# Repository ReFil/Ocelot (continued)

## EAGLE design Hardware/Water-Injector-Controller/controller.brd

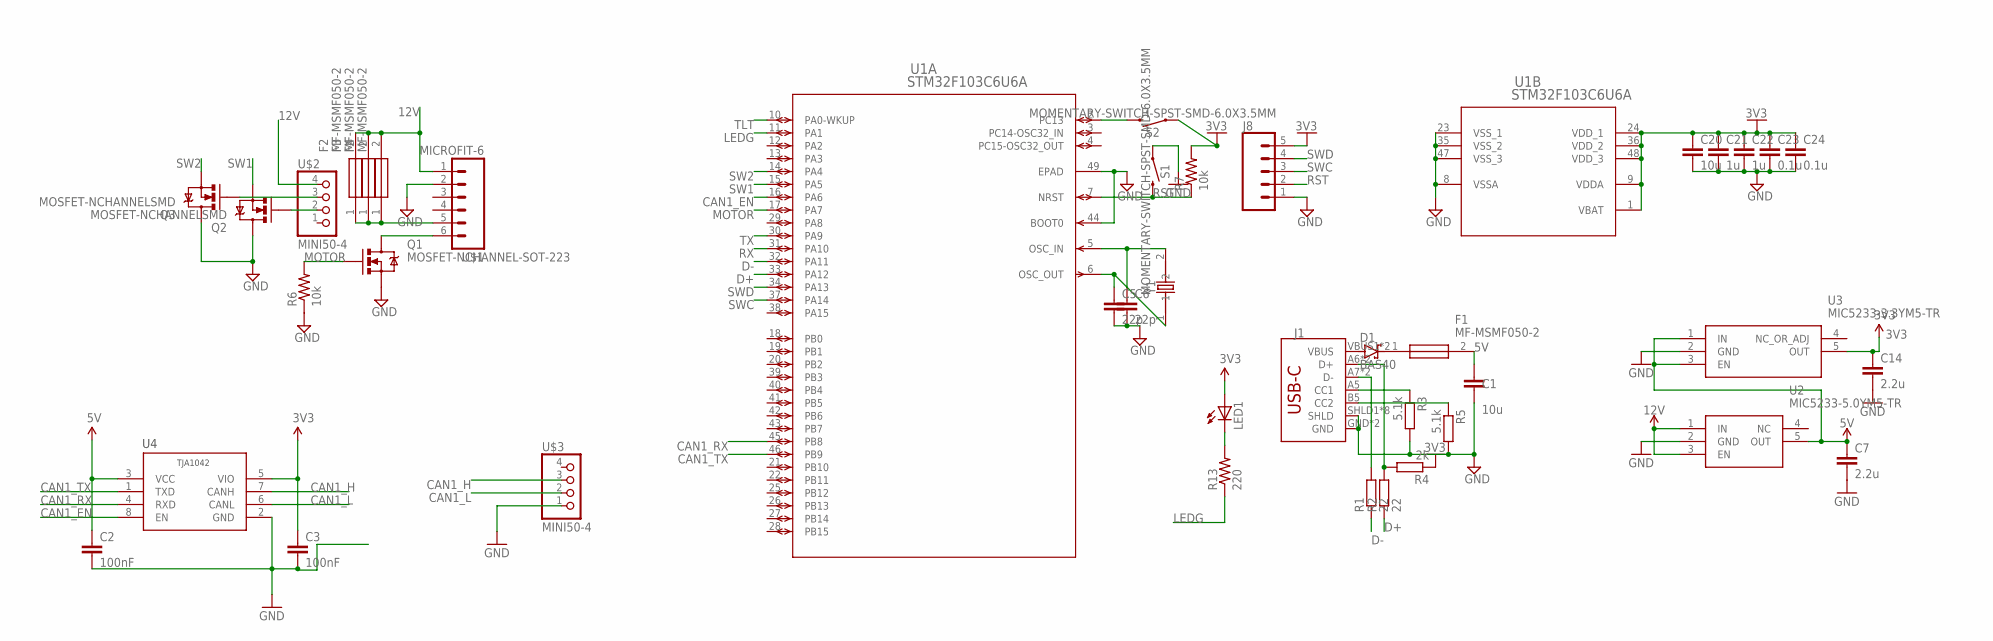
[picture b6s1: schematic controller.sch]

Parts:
C1: 10u; 0603-C
C2, C3: 100nF; 0603-C
C5, C6: 22p; C1206
C7, C14: 2.2u; C0603
C20: 10u; C1206
C21, C22: 1u; C1206
C23, C24: 0.1u; C1206
D1: BAS40; SOT23
F1, F2, F3, F4: MF-MSMF050-2; FUSC4632X85N
J1: SPARKFUN-CONNECTORS_USB_C16PIN; SPARKFUN-CONNECTORS_USB-C-16P
J8: CONN_051.27MM; 1X05_1.27MM
LED1: LEDCHIPLED_0805; CHIPLED_0805
Q1: MOSFET-NCHANNEL-SOT-223; SOT-223
Q2, Q3: MOSFET-NCHANNELSMD; SOT23-3
R1, R2: 22; R1206
R3, R5: 5.1k; R1206
R4: 2k; R1206
R6, R7: 10k; 0402-R
R13: 220; 0402-R
S1, S2: MOMENTARY-SWITCH-SPST-SMD-6.0X3.5MM; TACTILE_SWITCH_SMD_6.0X3.5MM
U1: STM32F103C6U6A; UFQFPN-48_7X7X0P55MM
U2: MIC5233-5.0YM5-TR; SOT95P280X145-5N
U3: MIC5233-3.3YM5-TR; SOT95P280X145-5N
U4: TJA1042; NXP_SEMICONDUCTORS_TJA1042T-3-CM_118_0
U$1: MICROFIT-6
U$2, U$3: MINI50-4; MINI50
Y1: 8MHz; OSCCC500X320X135

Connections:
3V3: C3.1, C14.1, C20.1, C21.1, C22.1, C23.1, C24.1, J8.5, LED1.A, R4.1, R7.2, S2.1, U1.1 (VBAT), U1.9 (VDDA), U1.24 (VDD_1), U1.36 (VDD_2), U1.48 (VDD_3), U3.5 (OUT), U4.5 (VIO)
5V: C1.1, C2.1, C7.1, F1.2, U2.5 (OUT), U3.1 (IN), U3.3 (EN), U4.3 (VCC)
12V: F2.2, F3.2, F4.2, U2.1 (IN), U2.3 (EN), U$1.1, U$2.4 (1)
CAN1_EN: U1.16 (PA6), U4.8 (EN)
CAN1_H: U4.7 (CANH), U$3.3 (2)
CAN1_L: U4.6 (CANL), U$3.2 (3)
CAN1_RX: U1.45 (PB8), U4.4 (RXD)
CAN1_TX: U1.46 (PB9), U4.1 (TXD)
D+: R2.1, U1.33 (PA12)
D-: R1.1, U1.32 (PA11)
GND: C1.2, C2.2, C3.2, C5.2, C6.2, C7.2, C14.2, C20.2, C21.2, C22.2, C23.2, C24.2, J1.GND, J1.GND2 (GND), J1.SHLD1 (SHLD), J1.SHLD2 (SHLD), J1.SHLD3 (SHLD), J1.SHLD4 (SHLD), J1.SHLD5 (SHLD), J1.SHLD6 (SHLD), J1.SHLD7 (SHLD), J1.SHLD8 (SHLD), J8.1, Q1.3 (S), Q2.3 (D), Q3.3 (D), R3.2, R5.2, R6.1, S1.1, U1.8 (VSSA), U1.23 (VSS_1), U1.35 (VSS_2), U1.44 (BOOT0), U1.47 (VSS_3), U1.49 (EPAD), U2.2 (GND), U3.2 (GND), U4.2 (GND), U$1.2, U$3.1 (4)
LEDG: R13.1, U1.11 (PA1)
MOTOR: Q1.1 (G), R6.2, U1.17 (PA7)
unnamed: S2.2, U1.2 (PC13)
unnamed: Q2.1 (G), U$2.2 (3)
unnamed: F2.1, F3.1, F4.1, U$1.5
unnamed: Q3.1 (G), U$2.3 (2)
unnamed: Q1.2 (D), Q1.4 (D), U$1.6
unnamed: D1.1 (A), J1.VBUS1 (VBUS), J1.VBUS2 (VBUS)
unnamed: D1.3 (C), F1.1
unnamed: C6.1, U1.5 (OSC_IN), Y1.2
unnamed: C5.1, U1.6 (OSC_OUT), Y1.1
unnamed: J1.A5 (CC1), R3.1
unnamed: J1.B5 (CC2), R5.1
unnamed: J1.A7 (D-), J1.B7 (D-), R1.2
unnamed: J1.A6 (D+), J1.B6 (D+), R2.2, R4.2
unnamed: LED1.C, R13.2
RST: J8.2, R7.1, S1.2, U1.7 (NRST)
RX: U1.31 (PA10)
SW1: Q2.2 (S), U1.15 (PA5)
SW2: Q3.2 (S), U1.14 (PA4)
SWC: J8.3, U1.37 (PA14)
SWD: J8.4, U1.34 (PA13)
TLT: U1.10 (PA0-WKUP)
TX: U1.30 (PA9)

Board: 2 copper layers, 41 parts (0 on the bottom side), 32 nets, no tracks yet.

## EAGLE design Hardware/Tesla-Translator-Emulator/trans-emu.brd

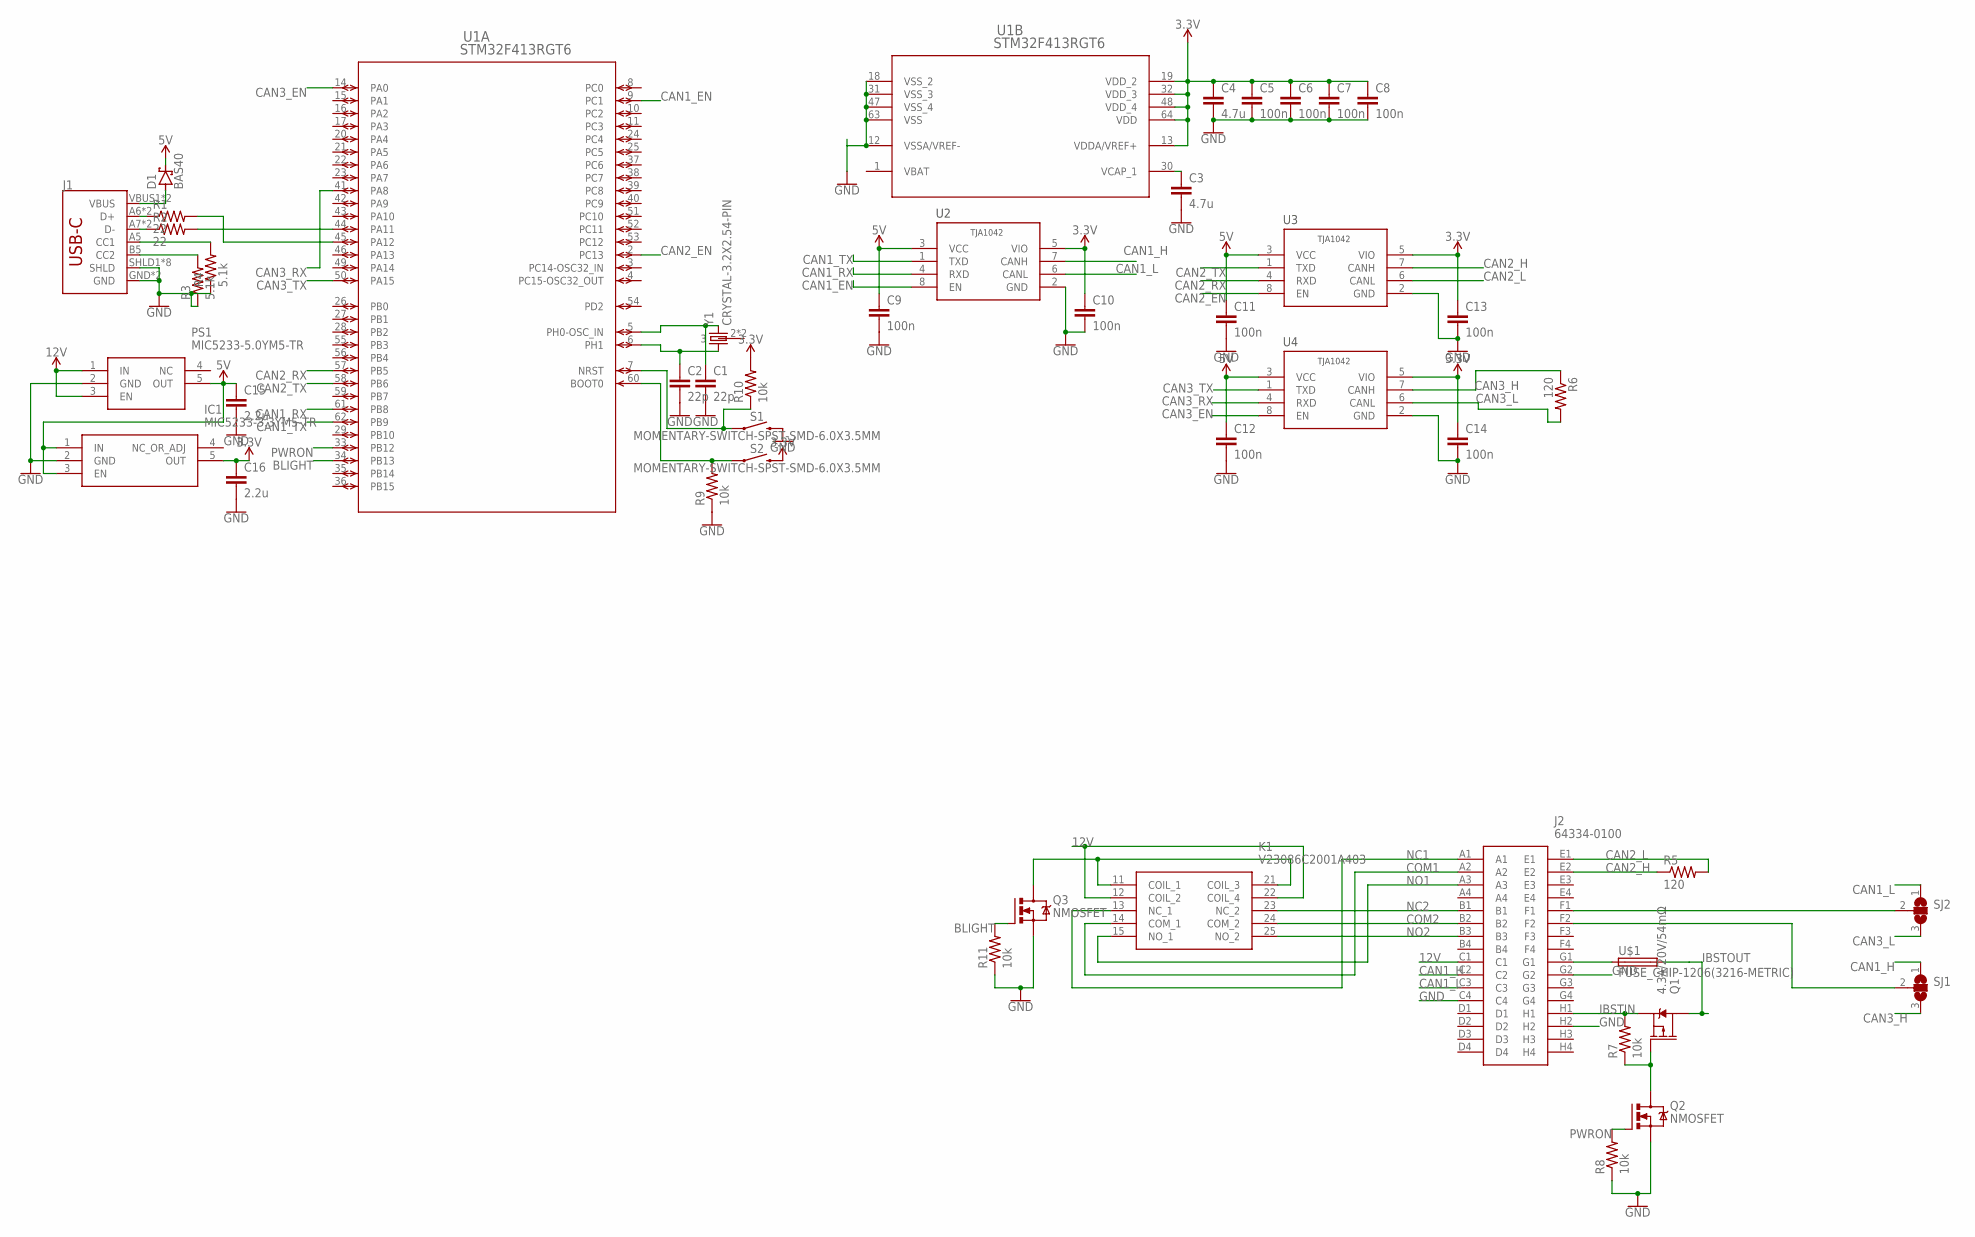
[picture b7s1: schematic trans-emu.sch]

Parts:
C1, C2: 22p; 0603-C
C3, C4: 4.7u; 0603-C
C5, C6, C7, C8, C9, C10, C11, C12, C13, C14: 100n; 0603-C
C15, C16: 2.2u; 0603-C
D1: BAS40; SOT23
IC1: MIC5233-3.3YM5-TR; SOT95P280X145-5N
J1: USB-C-BREAKOUT_SPARKFUN-CONNECTORS_USB_C16PIN; USB-C-BREAKOUT_SPARKFUN-CONNECTORS_USB-C-16P
J2: 64334-0100; 643340100
K1: V23086C2001A403
PS1: MIC5233-5.0YM5-TR; SOT95P280X145-5N
Q1: 4.3A/20V/54mΩ; SOT23-3
Q2, Q3: NMOSFET; SOT23
R1, R2: 22; 0402-R
R3, R4: 5.1k; 0402-R
R5, R6: 120; 0402-R
R7, R8, R9, R10, R11: 10k; 0402-R
S1, S2: MOMENTARY-SWITCH-SPST-SMD-6.0X3.5MM; TACTILE_SWITCH_SMD_6.0X3.5MM
SJ1, SJ2: SJ2W; SJ_2
U1: STM32F413RGT6; LQFP64-10X10MM
U2, U3, U4: TJA1042; NXP_SEMICONDUCTORS_TJA1042T-3-CM_118_0
U$1: FUSE_CHIP-1206(3216-METRIC); FUSC3215X82N
Y1: CRYSTAL-3.2X2.54-PIN; XTAL-3.2X2.5

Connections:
3.3V: C4.1, C5.1, C6.1, C7.1, C8.1, C10.1, C13.1, C14.1, C16.1, IC1.5 (OUT), R10.2, S2.2, U1.13 (VDDA/VREF+), U1.19 (VDD_2), U1.32 (VDD_3), U1.48 (VDD_4), U1.64 (VDD), U2.5 (VIO), U3.5 (VIO), U4.5 (VIO)
5V: C9.1, C11.1, C12.1, C15.1, D1.3 (C), IC1.1 (IN), IC1.3 (EN), PS1.5 (OUT), U2.3 (VCC), U3.3 (VCC), U4.3 (VCC)
12V: J2.C1, K1.12 (COIL_2), K1.22 (COIL_4), PS1.1 (IN), PS1.3 (EN)
BLIGHT: Q3.1 (G), R11.2, U1.34 (PB13)
CAN1_EN: U1.9 (PC1), U2.8 (EN)
CAN1_H: J2.C2, SJ1.1, U2.7 (CANH)
CAN1_L: J2.C3, SJ2.1, U2.6 (CANL)
CAN1_RX: U1.61 (PB8), U2.4 (RXD)
CAN1_TX: U1.62 (PB9), U2.1 (TXD)
CAN2_EN: U1.2 (PC13), U3.8 (EN)
CAN2_H: J2.E2, R5.1, U3.7 (CANH)
CAN2_L: J2.E1, R5.2, U3.6 (CANL)
CAN2_RX: U1.57 (PB5), U3.4 (RXD)
CAN2_TX: U1.58 (PB6), U3.1 (TXD)
CAN3_EN: U1.14 (PA0), U4.8 (EN)
CAN3_H: R6.1, SJ1.3, U4.7 (CANH)
CAN3_L: R6.2, SJ2.3, U4.6 (CANL)
CAN3_RX: U1.41 (PA8), U4.4 (RXD)
CAN3_TX: U1.50 (PA15), U4.1 (TXD)
COM1: J2.A2, K1.14 (COM_1)
COM2: J2.B2, K1.24 (COM_2)
GND: C1.2, C2.2, C3.2, C4.2, C5.2, C6.2, C7.2, C8.2, C9.2, C10.2, C11.2, C12.2, C13.2, C14.2, C15.2, C16.2, IC1.2 (GND), J1.GND, J1.GND2 (GND), J1.SHLD1 (SHLD), J1.SHLD2 (SHLD), J1.SHLD3 (SHLD), J1.SHLD4 (SHLD), J1.SHLD5 (SHLD), J1.SHLD6 (SHLD), J1.SHLD7 (SHLD), J1.SHLD8 (SHLD), J2.C4, J2.G2, J2.H2, PS1.2 (GND), Q2.2 (S), Q3.2 (S), R3.1, R4.1, R8.1, R9.1, R11.1, S1.2, U1.12 (VSSA/VREF-), U1.18 (VSS_2), U1.31 (VSS_3), U1.47 (VSS_4), U1.63 (VSS), U2.2 (GND), U3.2 (GND), U4.2 (GND)
IBSTIN: J2.H1, Q1.2 (S), R7.2
IBSTOUT: Q1.3 (D), U$1.2
unnamed: C1.1, U1.5 (PH0-OSC_IN), Y1.3 (2)
unnamed: C2.1, U1.6 (PH1), Y1.1
unnamed: R2.2, U1.44 (PA11)
unnamed: R1.2, U1.45 (PA12)
unnamed: D1.1 (A), J1.VBUS1 (VBUS), J1.VBUS2 (VBUS)
unnamed: J1.A5 (CC1), R4.2
unnamed: J1.B5 (CC2), R3.2
unnamed: R10.1, S1.1, U1.7 (NRST)
unnamed: R9.2, S2.1, U1.60 (BOOT0)
unnamed: J1.A6 (D+), J1.B6 (D+), R1.1
unnamed: J1.A7 (D-), J1.B7 (D-), R2.1
unnamed: J2.F2, SJ1.2
unnamed: C3.1, U1.30 (VCAP_1)
unnamed: J2.F1, SJ2.2
unnamed: Q1.1 (G), Q2.3 (D), R7.1
unnamed: K1.11 (COIL_1), K1.21 (COIL_3), Q3.3 (D)
unnamed: J2.G1, U$1.1
NC1: J2.A1, K1.13 (NC_1)
NC2: J2.B1, K1.23 (NC_2)
NO1: J2.A3, K1.15 (NO_1)
NO2: J2.B3, K1.25 (NO_2)
PWRON: Q2.1 (G), R8.2, U1.33 (PB12)
VBAT: U1.1 (VBAT)

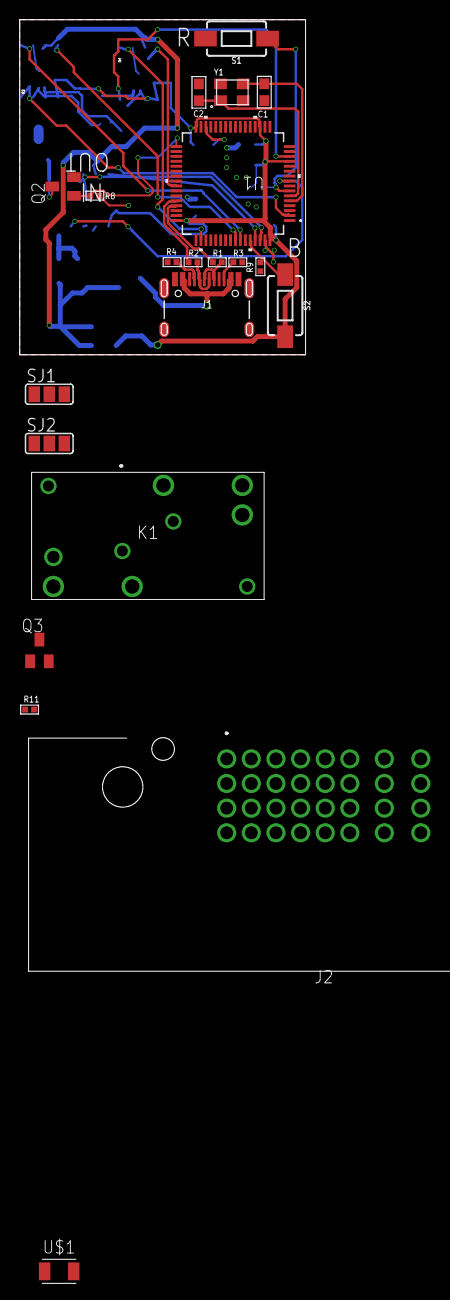
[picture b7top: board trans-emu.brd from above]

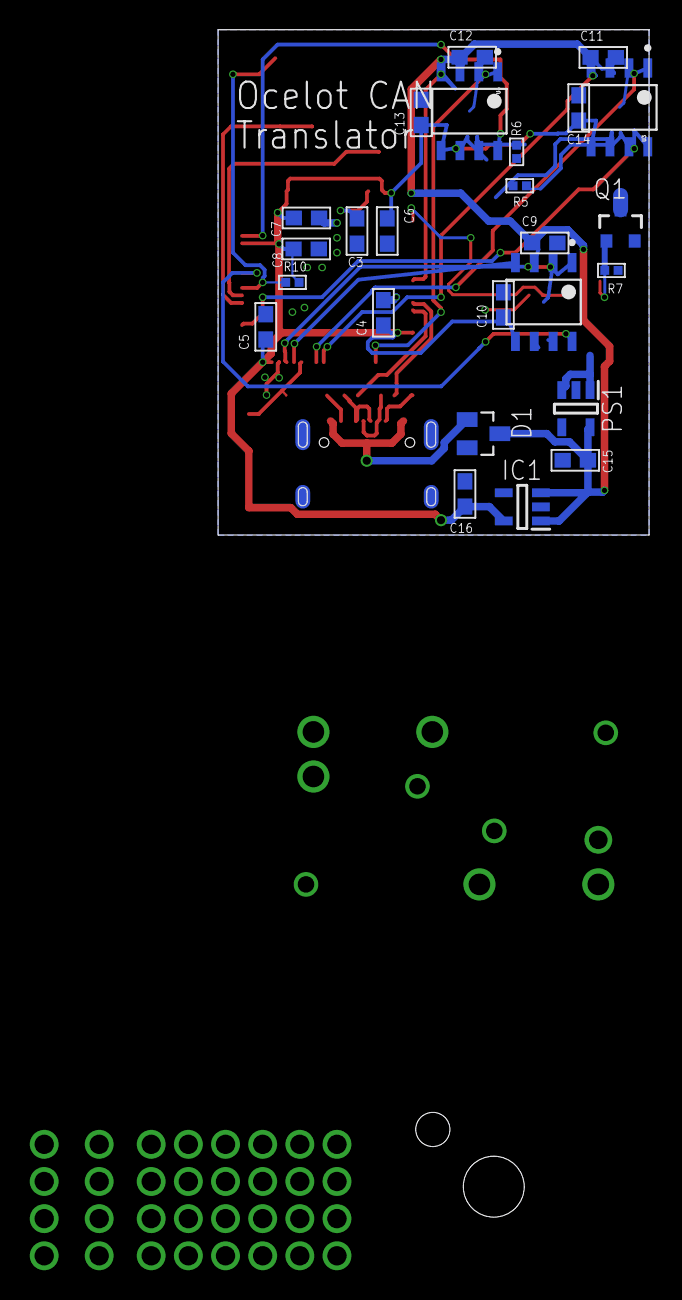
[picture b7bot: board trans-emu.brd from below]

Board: 2 copper layers, 29.0 x 34.0 mm, 46 parts (25 on the bottom side), 46 nets.

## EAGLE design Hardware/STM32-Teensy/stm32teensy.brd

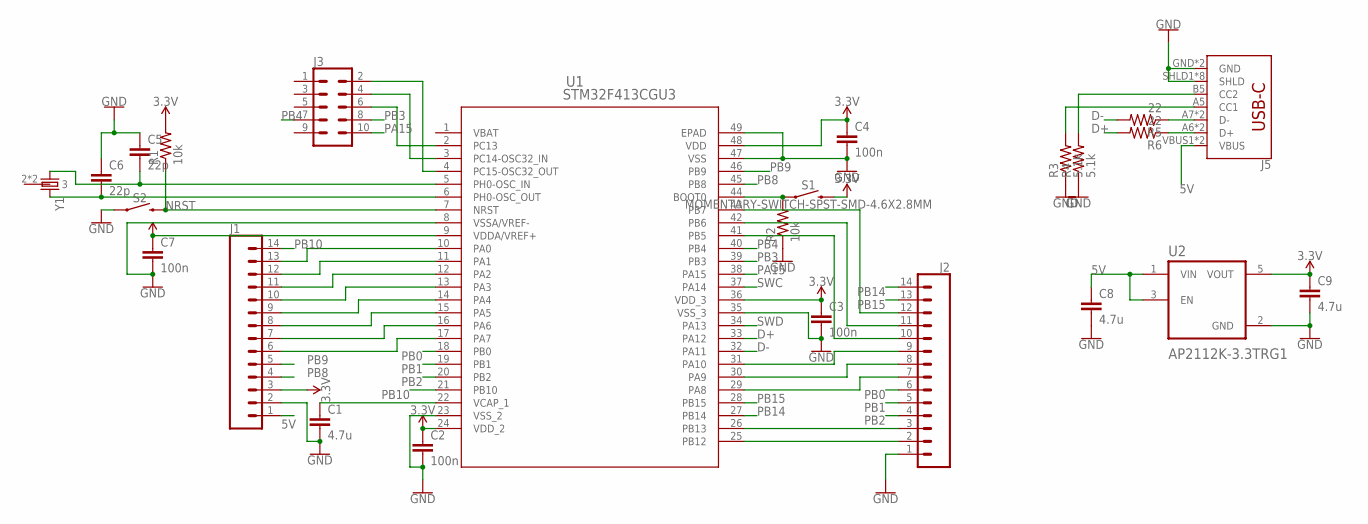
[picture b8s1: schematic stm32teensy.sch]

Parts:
C1, C8, C9: 4.7u; 0402-C
C2, C3, C4, C7: 100n; 0402-C
C5, C6: 22p; 0402-C
J1, J2: CONN_14; 1X14
J3: CONN_05X2SHD_SMD; 2X5-SHROUDED_SMD
J5: SPARKFUN-CONNECTORS_USB_C16PIN; SPARKFUN-CONNECTORS_USB-C-16P
R1, R2: 10k; 0402-R
R3, R4: 5.1k; 0402-R
R5, R6: 22; 0402-R
S1, S2: MOMENTARY-SWITCH-SPST-SMD-4.6X2.8MM; TACTILE_SWITCH_SMD_4.6X2.8MM
U1: STM32F413CGU3; UFQFPN_13CGU3_STM
U2: AP2112K-3.3TRG1; SOT95P285X140-5N
Y1: CRYSTAL-3.2X2.54-PIN; XTAL-3.2X2.5

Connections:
3.3V: C2.1, C3.1, C4.1, C7.1, C9.1, J1.3, R1.2, S1.3 (2), S1.4 (2), U1.9 (VDDA/VREF+), U1.24 (VDD_2), U1.36 (VDD_3), U1.48 (VDD), U2.5 (VOUT)
5V: C8.1, J1.1, J5.VBUS1 (VBUS), J5.VBUS2 (VBUS), U2.1 (VIN), U2.3 (EN)
D+: R6.2, U1.33 (PA12)
D-: R5.2, U1.32 (PA11)
GND: C1.2, C2.2, C3.2, C4.2, C5.1, C6.1, C7.2, C8.2, C9.2, J1.2, J2.1, J5.GND, J5.GND2 (GND), J5.SHLD1 (SHLD), J5.SHLD2 (SHLD), J5.SHLD3 (SHLD), J5.SHLD4 (SHLD), J5.SHLD5 (SHLD), J5.SHLD6 (SHLD), J5.SHLD7 (SHLD), J5.SHLD8 (SHLD), R2.1, R3.1, R4.1, S2.1, S2.2 (1), U1.8 (VSSA/VREF-), U1.23 (VSS_2), U1.35 (VSS_3), U1.47 (VSS), U1.49 (EPAD), U2.2 (GND)
unnamed: J3.6, U1.2 (PC13)
unnamed: R2.2, S1.1, S1.2 (1), U1.44 (BOOT0)
unnamed: C6.2, U1.6 (PH0-OSC_OUT), Y1.3 (2)
unnamed: C5.2, U1.5 (PH0-OSC_IN), Y1.1
unnamed: J1.13, U1.10 (PA0)
unnamed: J2.10, U1.41 (PB5)
unnamed: C1.1, U1.22 (VCAP_1)
unnamed: J1.12, U1.11 (PA1)
unnamed: J1.11, U1.12 (PA2)
unnamed: J1.10, U1.13 (PA3)
unnamed: J1.9, U1.14 (PA4)
unnamed: J1.8, U1.15 (PA5)
unnamed: J1.7, U1.16 (PA6)
unnamed: J1.6, U1.17 (PA7)
unnamed: J2.2, U1.25 (PB12)
unnamed: J2.3, U1.26 (PB13)
unnamed: J2.11, U1.42 (PB6)
unnamed: J2.12, U1.43 (PB7)
unnamed: J2.7, U1.29 (PA8)
unnamed: J2.8, U1.30 (PA9)
unnamed: J2.9, U1.31 (PA10)
unnamed: J3.4, U1.3 (PC14-OSC32_IN)
unnamed: J3.2, U1.4 (PC15-OSC32_OUT)
unnamed: J5.A7 (D-), J5.B7 (D-), R5.1
unnamed: J5.A6 (D+), J5.B6 (D+), R6.1
unnamed: J5.A5 (CC1), R3.2
unnamed: J5.B5 (CC2), R4.2
NRST: R1.1, S2.3 (2), S2.4 (2), U1.7 (NRST)
PA15: J3.10, U1.38 (PA15)
PB0: J2.6, U1.18 (PB0)
PB1: J2.5, U1.19 (PB1)
PB2: J2.4, U1.20 (PB2)
PB3: J3.8, U1.39 (PB3)
PB4: J3.7, U1.40 (PB4)
PB8: J1.4, U1.45 (PB8)
PB9: J1.5, U1.46 (PB9)
PB10: J1.14, U1.21 (PB10)
PB14: J2.14, U1.27 (PB14)
PB15: J2.13, U1.28 (PB15)
SWC: U1.37 (PA14)
SWD: U1.34 (PA13)

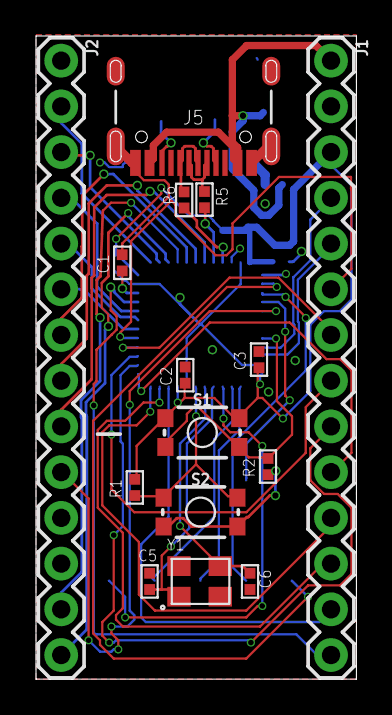
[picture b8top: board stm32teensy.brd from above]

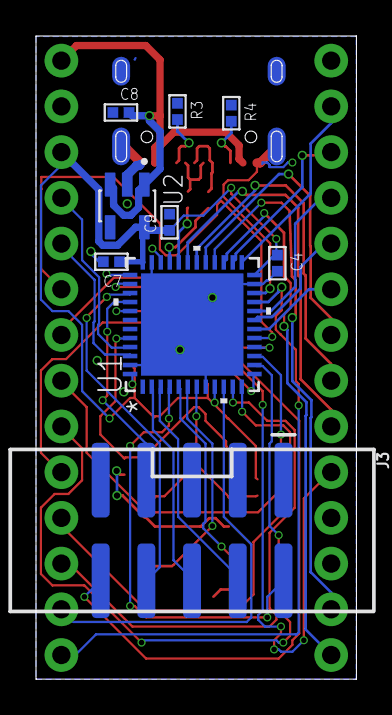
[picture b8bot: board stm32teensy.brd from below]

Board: 2 copper layers, 17.8 x 35.7 mm, 24 parts (9 on the bottom side), 44 nets.

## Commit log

2021-01-22 Pedal commit
2021-01-22 add mounting holes
2021-01-23 Button controller commit
2021-01-24 Software commit
2021-01-24 Car harness
2021-01-25 clearance and power
2021-01-25 schematic complete board start ranlator emulator
2021-01-25 yaw commit
2021-01-26 boards
2021-01-28 final board prep for manufacture
2021-01-29 signal switching
2021-01-29 software
2021-02-15 renaming
2021-03-06 Pedal fix
2021-03-09 BOM2
2021-03-11 add pull resistors
2021-03-16 new boards
2021-03-19 Eon control board schematic
2021-03-25 Pedal v2
2021-04-01 ibooster v2, stm32teensy work
2021-04-02 stm32 teensy board
2021-04-04 Ibooster board updates
2021-04-07 ibooster schematic and water controller
2021-04-15 Gateway rev2
2021-04-19 ibooster gateway
2021-04-20 swd header
2021-04-22 eoncontrol boared
2021-04-27 qfp64 commit
2021-04-28 motor driver breakout
2021-09-08 pandaless interface
2021-12-17 some shit
2022-03-21 new thingy
2022-03-22 add gnd
2022-03-25 new vgerd
2025-01-16 Mfg files
